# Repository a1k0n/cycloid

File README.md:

Self-racing robot using either ceiling lights or traffic cones to localize.
Very much a work in progress and documentation will always be severely
lacking as this is a constantly moving target!

This is my ongoing entry in the quarterly [DIY Robocars
competition](https://diyrobocars.com/") in Oakland, CA.

## Hardware (updated!)

I've switched to a 1/10th scale touring car (for flat ground courses) as it
handles much better and also eliminates the very finicky wheel encoders used on
the Rustler.

Touring car:

 - HobbyKing Blaze R2 ($99)
 - Turnigy TrackStar 9.5T sensored brushless motor 4120KV ($34)
 - Turnigy TrackStar 80A brushless sensored ESC ($40)
 - TrackStar TS-411MG digital servo ($17)
 - Basher 6600mAh 2S2P 40C hardcase LiHV pack ($38) (smaller batteries are
   fine, but I like being able to run the computer all day on one charge)
 - Tires appropriate for track (Schumacher Racing SST Mini Pins are the way to go on carpet)

Electronics:

 - Raspberry Pi 3 B ($35)
 - SanDisk Ultra 32GB microSDHC UHS-I Card ($9) -- it's important to have the
   right kind of SD card or it won't keep up with recordings, and it's hard to
   tell ahead of time which ones will work.
 - Arducam OV5647 Raspberry Pi 3 camera with LS-40180 fisheye lens ($30)
 - ILI9340 SPI 240x320 LCD display, via the fbtft device driver (about $7)
 - Some XT60 plugs and an extra 6-wire brushless sensor cable (~$10)
 - Logitech F710 wireless game pad w/ USB dongle (~$40)
 - Custom HAT board w/ STM32F030 and ICM-20600 IMU: https://easyeda.com/a1k0n/cycloid (PCB +
   parts is about $5 apiece in qty 10 from JLPCB / LCSC, plus you have to
   solder it all together)

Total hardware cost for the car comes to under $350, plus the cost of the
wireless controller (~$40).

### 3D printed mounting parts

Besides the RC car, there are three 3D-printed parts to mount the camera and
electronics for various cars (Blaze R2, Traxxas Rustler, Exceed Magnet,
WLToys K989). I drill and tap 2.5mm screw holes in most of them. These are
all modeled in OpenSCAD and source code and .stl files are in `hw/scad/`.

### Configurations

There is a mandatory configuration file called `cycloid.ini` which allows you
to specify the mode of communication to the ESC and servos (Cycloid HAT
board, GPIO pins supported; code also exists for Teensy and PCA9685) as well
as specify which IMU (all Invensense MPU-9x50, MPU-6050, ICM-2060x supported)

See `cycloid.ini.example` for full details.

### Defining a race track

 - `tools/ceilslam` has code to turn a datalog saved from the car into a
 birds-eye view of the track based on ceiling light tracking and reprojecting
 the pixels which can see the floor.

 - `tools/trackplan/gui.py` contains a Dear Imgui-based application for
 defining a racetrack boundary (and cone locations) given a birdseye view of
 the track. It can also get a birdseye view of the track given two different
 views and matching sets of points.

## Code

Can be compiled on a host PC with a cross compiler (e.g. on macOS you can
install this: https://www.jaredwolff.com/toolchains/) or on the Raspberry Pi
itself.

If you want to build the code, clone with `git clone --recursive
https://github.com/a1k0n/cycloid` in order to get the Raspberry Pi userland
submodule (otherwise just run `git submodule init` and `git submodule update`).

Here's how I build it:

Once you have a raspberry pi cross compiler (see two paragraphs above), edit
`crosscompile.cmake` to point to the correct compiler name / path, and do this:

```
$ mkdir build
$ cd build
$ cmake -DCMAKE_TOOLCHAIN_FILE=../crosscompile.cmake ../src -DCMAKE_BUILD_TYPE=RelWithDebInfo
$ make -j4
```

The main executable will be in `build/drive/drive`; scp that to your raspberry
pi on the car, create a `cycloid.ini`, pair a joystick, and run it.

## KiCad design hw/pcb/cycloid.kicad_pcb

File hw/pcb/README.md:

This is a PCB which carries the Teensy 3.2 and connects to the servo & speed
controller on the car, as well as the stock R/C radio, wheel encoders, and an
analog feedback tap from the servo's internal potentiometer (requires modifying
servo).

It has the same mounting holes as the PCA9685 I2C PWM expander board commonly
used for the purpose of connecting a Raspberry Pi to an R/C car.

It can be seen (and purchased) here: 

</img>
<br>
<a href="https://oshpark.com/shared_projects/DP0wzTcU">order on OSHPark</a>

(Note that I have a ton of extras; if you ask me at an Oakland DIYRobocars race
I'll give you one)

It also has an i2c piggyback connection for the IMU.

R1 and R2 are pull-up resistors for I2C; I do not recommend populating them,
however.

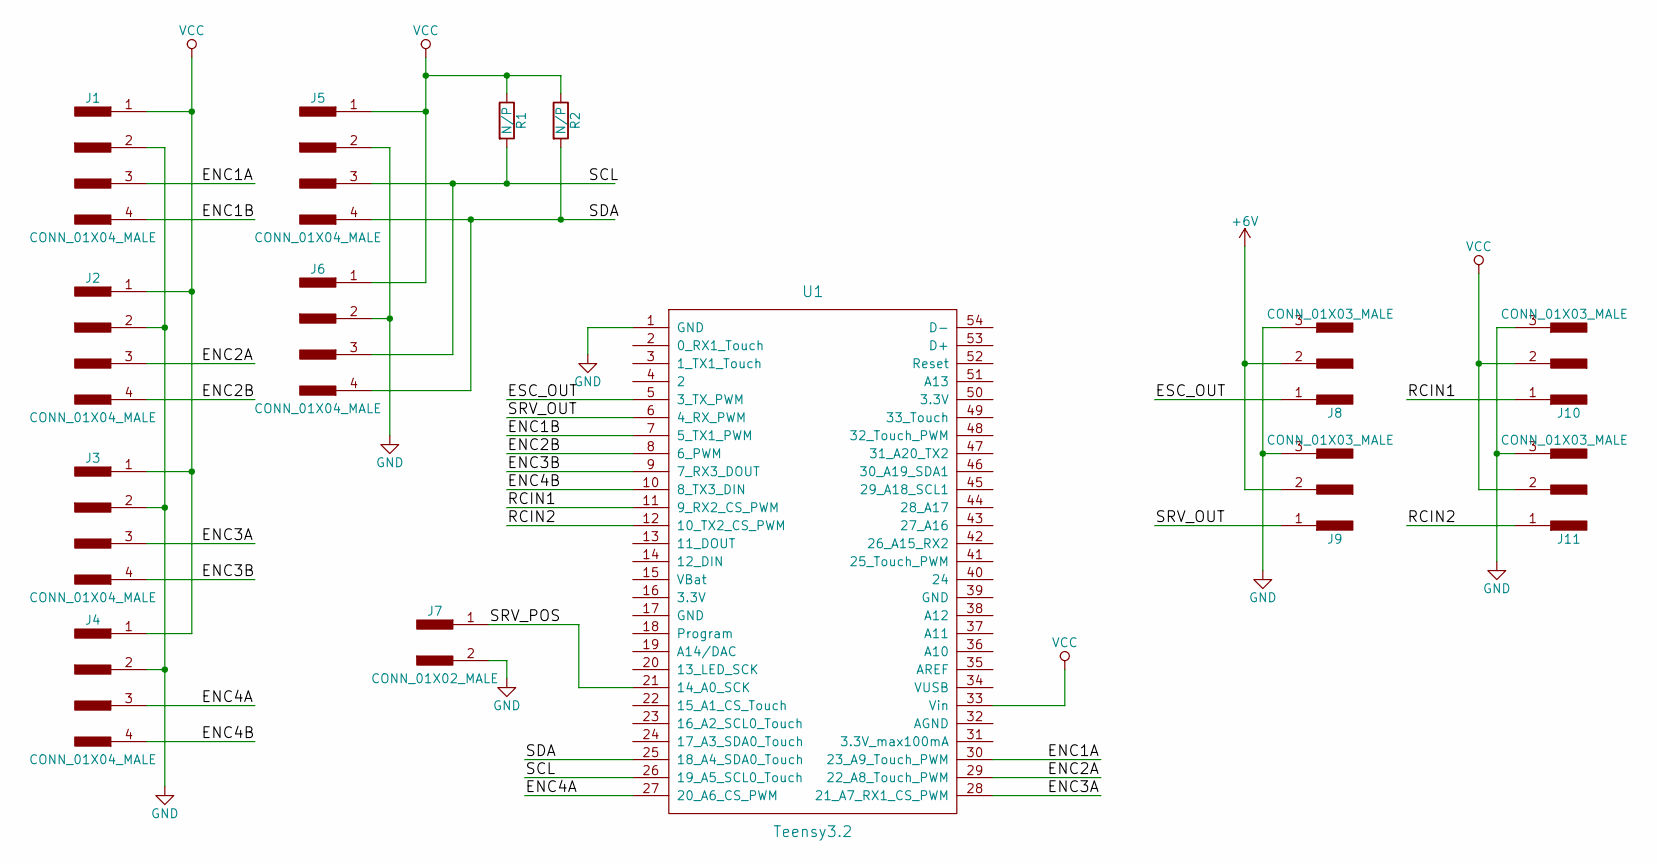
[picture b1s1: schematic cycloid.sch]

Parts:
J1, J2, J3, J4, J5, J6: CONN_01X04_MALE; Pin_Header_Straight_1x04_Pitch2.54mm
J7: CONN_01X02_MALE; Pin_Header_Straight_1x02_Pitch2.54mm
J8, J9, J10, J11: CONN_01X03_MALE; Pin_Header_Straight_1x03_Pitch2.54mm
R1, R2: N/P; R_0805_HandSoldering
U1: Teensy3.2; Teensy30_31_32_LC

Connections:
+6V: J8.2, J9.2
/ENC1A: J1.3, U1.30 (23_A9_Touch_PWM)
/ENC1B: J1.4, U1.7 (5_TX1_PWM)
/ENC2A: J2.3, U1.29 (22_A8_Touch_PWM)
/ENC2B: J2.4, U1.8 (6_PWM)
/ENC3A: J3.3, U1.28 (21_A7_RX1_CS_PWM)
/ENC3B: J3.4, U1.9 (7_RX3_DOUT)
/ENC4A: J4.3, U1.27 (20_A6_CS_PWM)
/ENC4B: J4.4, U1.10 (8_TX3_DIN)
/ESC_OUT: J8.1, U1.5 (3_TX_PWM)
/RCIN1: J10.1, U1.11 (9_RX2_CS_PWM)
/RCIN2: J11.1, U1.12 (10_TX2_CS_PWM)
/SCL: J5.3, J6.3, R1.2, U1.26 (19_A5_SCL0_Touch)
/SDA: J5.4, J6.4, R2.2, U1.25 (18_A4_SDA0_Touch)
/SRV_OUT: J9.1, U1.6 (4_RX_PWM)
/SRV_POS: J7.1, U1.21 (14_A0_SCK)
GND: J1.2, J2.2, J3.2, J4.2, J5.2, J6.2, J7.2, J8.3, J9.3, J10.3, J11.3, U1.1 (GND)
VCC: J1.1, J2.1, J3.1, J4.1, J5.1, J6.1, J10.2, J11.2, R1.1, R2.1, U1.33 (Vin)

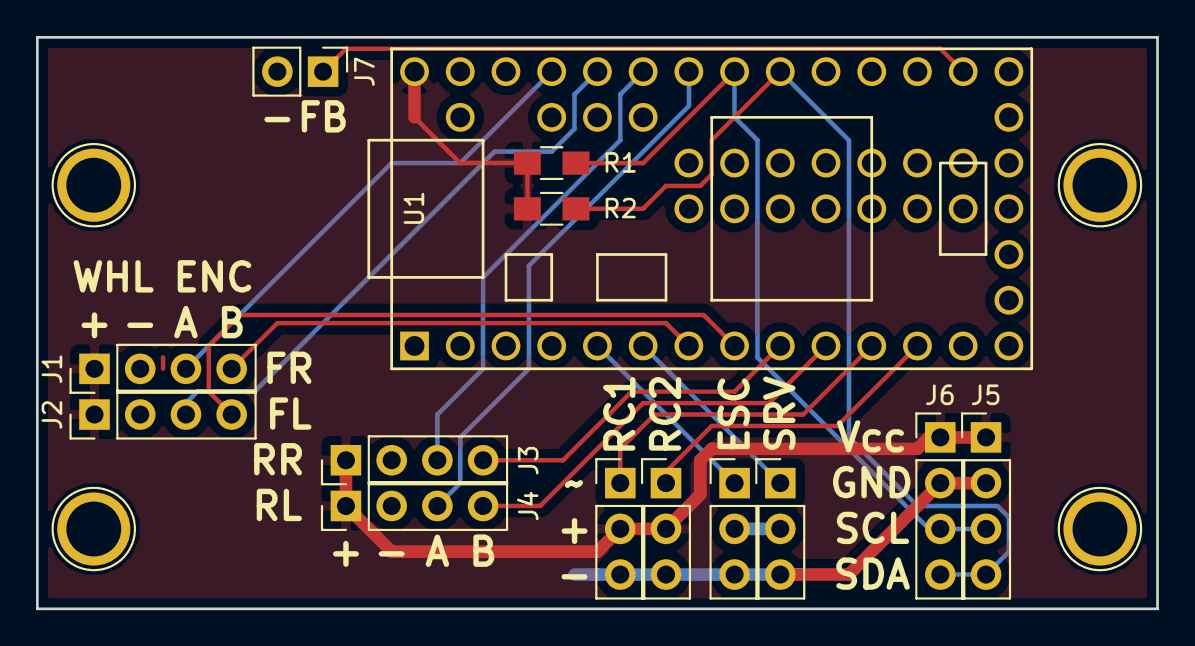
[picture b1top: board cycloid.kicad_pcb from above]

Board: 2 copper layers, 62.2 x 31.7 mm, 14 parts (0 on the bottom side), 18 nets.

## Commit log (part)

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2017-07-19 import phase 1
2017-08-06 getting there on the python code, still a lot of stuff to fix
2017-08-11 Add wheel encoder / servo feedback measurement
    also fix some bugs; e.g. heaviside was defined incorrectly
2017-08-12 smooth as butter now.
    still need to figure out what's wrong with the gyro updates.
2017-08-15 adding camera calibration, map generation, replay
2017-08-17 imgproc: compute center independent coord of quadratic fit
2017-08-19 static friction hack; seems to improve things a bit
2017-08-20 only record encoder period on falling edge
2017-08-21 add schematic pdf
    also make i2c pullups no-populate; we don't actually need or want them
2017-09-09 generate log-likelihood in python updates!
    very useful to get a number on how well the filter works.
    also, experimental code gen to support model-predictive control
2017-09-10 tweaked motor friction model...
    it still basically sucks, though.
2017-09-13 relay from birdseye view recordings
    no longer supports 320x140 U channel recordings
2017-09-14 adding rest of code
    need to fix build now
2017-09-14 make the code actually compile, re-add userland under src/
2017-09-14 wheel encoder readme
2017-09-14 add some readmes
2017-09-14 it works, except for these bugs
2017-09-15 fix jstest
2017-09-16 show annotate birdseye view on LCD
    pretty hacky but oh well
2017-09-16 add text drawing capability
    man that font is really small on the display though
2017-09-16 embiggen font, show config menu on display
2017-09-16 fix bug w/ saving/loading config
2017-10-10 centerline line localization; raceline trajectory
2017-10-11 switch to Wii U Pro Controller
    every single problem I had with the moga 2 controller just... completely
    went away. this is a much better controller.
2017-10-11 upgraded to raspbian stretch, now can use gcc5
2017-10-13 blah. experiment declared a failure.
2017-10-21 reverted motor model
    localization kinda works
    can't see the yellow line though
2017-10-21 3-pixel wide convolution
2017-11-08 don't trigger on pixels outside the FOV!
2017-11-20 make y/u/v classifier configurable
2018-08-07 disable localize, camera recal tweaks
2018-08-07 working velocity and yaw PI control! yeehaw!
2018-08-11 add basic particle filter version
    needs tuning; looking for an effective likelihood criterion
2018-08-14 Rao-Blackwellized particle filter
    Can recover cone locations from an empty initialization
    In this experiment here, the location of the first cone is fixed, just
    so that it lines up with the overhead map.
2018-08-14 cosmetic
2018-08-16 C++ localization seems to be working; pretty happy with that for now
2018-08-16 show cone detections on screen
2018-08-17 lut const thing
2018-08-17 find closest point / normal / curvature on track
2018-08-18 competition version 2018/8/18
2018-08-19 we're gonna need a bigger readme
2018-08-19 add trackmap.jpg to the repo
2018-08-24 control speed based on front/rear wheel speed difference
    tries to maintain an optimal slip ratio for the front tire (the point
    where lateral velocity should still = 0 but the front tire is no longer
    statically gripping). we'll see if this works.
2018-10-08 add bogon rejection to coneslam C++
2018-10-08 datalog controller also
2018-10-09 fix some bugs (and a crash)
2018-10-09 fix simple but crippling bugs in coneslam/localize
2018-10-10 fix coordinate frame mixups; add simulator
    now it at least works in theory, and should be tunable to work in
    practice.
2018-10-10 minor comment changes
2018-10-12 update README with new video
2018-10-12 add camera information
2018-10-18 consider cone radius in coneslam; add lookahead and accel limit
    lookahead turns out to be a bad idea
    accel limit can sort of override traction control
2018-10-22 DOH! bug in lookahead caused us to use wrong speed during the race.
2018-11-07 use continuous ADC sampling mode on Teensy
2018-11-07 better "anti-cone" rejection; tweak localization noise
2018-11-07 update lookup table (y vanishing point changed)
2018-11-07 add "tape track" representation code
2018-11-09 make a test program for mpu9150/mpu9250
2018-11-30 ready for 2018/11/30 event @ Voyage
    - 16 bit wheel period from STM32 HAT
    - adjust accel filter on MPU-9250
    - adjust various coneslam python parameters to match blaze R1
2018-11-30 fix minor compiler warning
2018-11-30 python implementation of particle headings for understeer tracking
2018-11-30 add cone detections to recordings
2018-12-05 update README with updated hardware info
2018-12-06 Docker/Balena: Deal with git submodule
2018-12-08 document I2C and serial protocol for STM32 HAT
2018-12-08 deprecate teensy code
    the stm32 is a much better behaved i2c slave than the arduino wire
    library will ever be
2018-12-08 failsafe: if host doesn't send an update within 100ms, stop motors
2018-12-09 Docker: Disable Resin-image generation b/c of travis
2018-12-09 Create LICENSE
2018-12-13 Update trajtrack.cc
    using a new, adaptive method of finding the lookahead kappa along with the information about the distance to it.
2018-12-13 Update controller.cc
    make use of max kappa and it's distance from current position in deciding whether to apply the brakes or nah.
2018-12-14 Update trajtrack_test.cc
    added the equal to sign
2018-12-31 add STL files for Blaze R1 parts
2019-01-04 add code for ICM20600
2019-01-04 add RS232 control loop code (experimental)
2019-01-08 IMU: Enable easy switching between different IMU types in CMake
2019-01-08 Recordreader: Print maximum value and cleanup printing
2019-01-21 remove support for teensy in favor of stm32hat
2019-01-21 add fiducial marker-based birdseye view generator
2019-01-21 100Hz control loop (untested)
2019-04-08 new blaze mounting design, camera pointing up
2019-04-08 adjusted positioning and screw diameters
2019-04-12 blaze r1 updates
2019-04-12 python 3 stuff
2019-04-12 improve design of lcd riser
2019-04-15 bball court landmarks
2019-04-15 corrected bball landmarks
2019-04-16 360 WIP
2019-04-16 fisheye WIP
2019-04-16 coneslam 360, totally hacked together on the C++ code side
2019-04-18 IFF chunk record reader
    still need to update all consumers:
    - pf.py / pf360.py / pf360.ipynb
2019-04-19 point picker utility
2019-04-20 gui wip
2019-04-20 getting close now
    optimization still doesn't work though
2019-04-20 optimizer only works with 100 points, i forgot
2019-04-21 edit home angle
2019-04-21 rotate camera 45 degrees
    wish i had thought of this sooner
2019-04-22 add trackexport to tapetrack
2019-04-24 45 deg camera adjustment, precaching data
2019-04-26 new motor / servo controller ideas
2019-04-26 2cm/px map export
2019-04-27 compile fix, add turn-in brake
2019-04-28 fix compile error, also insane curvatures in controller
2019-04-29 fix intellisense errors in vscode by caching cmake vars
2019-05-01 minor tool changes
    - trackplan can load older format
    - 2-parameter motor model fit rather than 3 (less likely to blow up)
2019-05-07 value function lookup
    solver to come
2019-05-09 valueiter: keep iterating until actually converged
2019-05-09 misc tweaks
2019-05-10 new value function driving thing
    might be working, not sure. fixed known bugs, can't test until tomorrow.
2019-05-12 fix fp16 definitions for travis
2019-05-14 interpolation of LUT, tweaked steering
2019-06-07 value function based driving stuff
    plus a new ceiling based slam algo
2019-06-29 don't let velocity go out of control
2019-07-01 fixes and updates from circuit launch 2019/06/29 race
2019-07-01 ceiling odometry
2019-07-07 attempt 1: windshield camera mount
2019-07-07 starting new bundle adjustment frontend
2019-07-07 aldjksf
2019-07-20 new magnet mounting
2019-07-21 remove unused constants
2019-07-22 ceiling tracking in C++
    totally optimized the matrix inversion with sympy. 300us/iteration
    (including image thresholding) on my mac; need to benchmark on RPi now
2019-07-22 fix bugs in RLE generator
2019-07-22 attempt to fix Travis build
2019-07-25 install libz to arm compiler so tests can compile
2019-07-26 make NEON code actually work
2019-08-02 ARM NEON tuning
2019-08-02 fp16 sse header
2019-08-02 checkpoint: fixing a bunch of crap under a time crunch
2019-08-02 ugh, this dumb one-liner caused my coordinates to all be messed up
2019-08-03 hack valueiter to have correct track width and do regular checkpoints
2019-08-08 switch back to regular gain-scheduled PI control
    previous PD transform was a flawed idea.
2019-08-12 8/11/2019 back-to-school testing
    - switch from Wii U controller to Logitech F710
    - plan assuming car continues for 60-90ms before control action is
    taken
    - test lots of curvature options, not just ones around current
    curvature.
    - log car config immediately on opening a recording file
2019-08-13 more plain ol' FPU optimizations
2019-08-13 whoops, wrong C++ cast
2019-08-18 add rpi zero cross-compile target
2019-08-18 making hw config flexible
2019-08-18 oops, fix compile, WIP
2019-08-19 moving stuff around, cleaning up
2019-08-19 fixing some extra junk
2019-08-19 add pigpio support
2019-09-14 fix a bunch of steering/driving configurability bugs
2019-09-14 oops, forgot to allow the control loop to exit
2019-09-14 add servo limits to config
2019-09-16 fix testdata
2019-09-17 make config human readable and autogen'd
2019-09-17 better handling of truncated files on recordreader
2019-09-19 fix some stuuuupid bugs in IMU velocity estimation
2019-09-19 use local h2f instead of __fp16
2019-09-19 visualize obstacles
2019-09-20 fix UI bug, zero-curvature bug, add new param
2019-09-20 hardcoded two configurable braking zones
2019-12-04 remove brakezone hack, add lap timer hack
2019-12-04 some UI fixes + starting on 4d value function + PyCUDA value iteration
2019-12-05 added collision penalties to cost
2019-12-05 minor but important tweaks in the value iteration kernel
2019-12-05 add missing floor mask editing junk
2019-12-06 motor parameter learning, setup for accel-based control
2019-12-06 not sure what the deal here was
2019-12-13 UI tweaks, planner / control fixes
    - show camera view and front view on UI
    - raise accelerometer bandwidth to ~50Hz
    - follow yaw rate in lookahead (was assuming understeering before)
2019-12-19 new fisheye model code; computes lookup tables from camera intrinsics
    still need to update the drive code and provide camera configs, fix test
    data
2020-02-13 get rid of fp16 stuff; use int16 fixed point and local fisheye model
2020-02-16 start gpsdrive main code
2020-02-19 starting gpsrover
2020-02-19 fix compilation
2020-02-19 log GPS stuff to stdout
2020-02-19 rename refactor for consistency
2020-02-19 add HMC5883L library support
2020-02-21 config menu UI
2020-02-21 minor fixes, actually works now
2020-02-24 velocity control, gps reference plane
2020-02-24 show track relative coordinates on screen
2020-02-25 bugfixes from track day
2020-02-28 some refactoring and better datalogging
2020-02-29 bugfixes
2020-02-29 bugfix bugfix
2020-03-01 compute front view lookup table on init
    removes need for frontlut.bin
2020-03-02 accidental dependency on lens for gpsdrive
    i probably won't bother to fix this ever
2020-03-05 add h264 recording
    however, it's dropping frames. it almost doesn't work at all.
2020-03-05 add kP steering-error control for gpsdrive as well
2020-03-07 code for 03/07/2020 event
2021-01-15 update tires in readme
2021-05-21 remove stupid lines
2021-05-23 some bugfixes/improvements, mostly dirty hacks
    This is the code that ran the 2021-05-22 race.
2021-08-17 Various fixes to make stuff work again; also added fps counter
2022-09-24 show which map is being used
2022-09-25 add policy network loader/evaluator
2022-09-29 add soft actor-critic training script
